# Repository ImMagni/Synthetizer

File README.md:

# Synthesizer 
A Synthesizer piano with three octaves that uses an Orpheus Pico, PCM5100 DAC, LM4810, and PAM8403 amplifiers.
 <br>

This project is a digital synthesizer keyboard capable of generating audio internally or outputting MIDI over USB. It features a screen-based user interface controlled through a rotary encoder and directional buttons.
## Features
- Volume control from the screen using a rotary encoder
- Selectable output modes: MIDI, Speakers, or Line output
- Three-octave keyboard
- Multiple waveform generation modes for audio
- Settings saves on memory
- On-screen menu system with directional navigation
- LCD feedback for current settings
## BOM
- 1× Orpheus_Pico (Raspberry Pi Pico)
- 5× Capacitor 1 µF
- 4× Capacitor 4.7 µF
- 1× Capacitor 0.1 µF
- 1× Capacitor 0.1 µF
- 2× Capacitor 10 µF
- 41× Diode 1N4148
- 1× screen ST7735R LCD
- 1× Jack audio 3.5 mm
- 2× Resistencia 10 kΩ
- 40× Cherry Switchs
- 1× Rotary Encoder with switch
- 1× PCM5100 DAC
- 1× LM4810
- 1x PAM8403
- 5x M3 Heatsets
- 5x M3x16 screws

Case|Schematic|Pcb
:-:|:-:|:-:|
|| 

-|-
:-:|:-:|
|

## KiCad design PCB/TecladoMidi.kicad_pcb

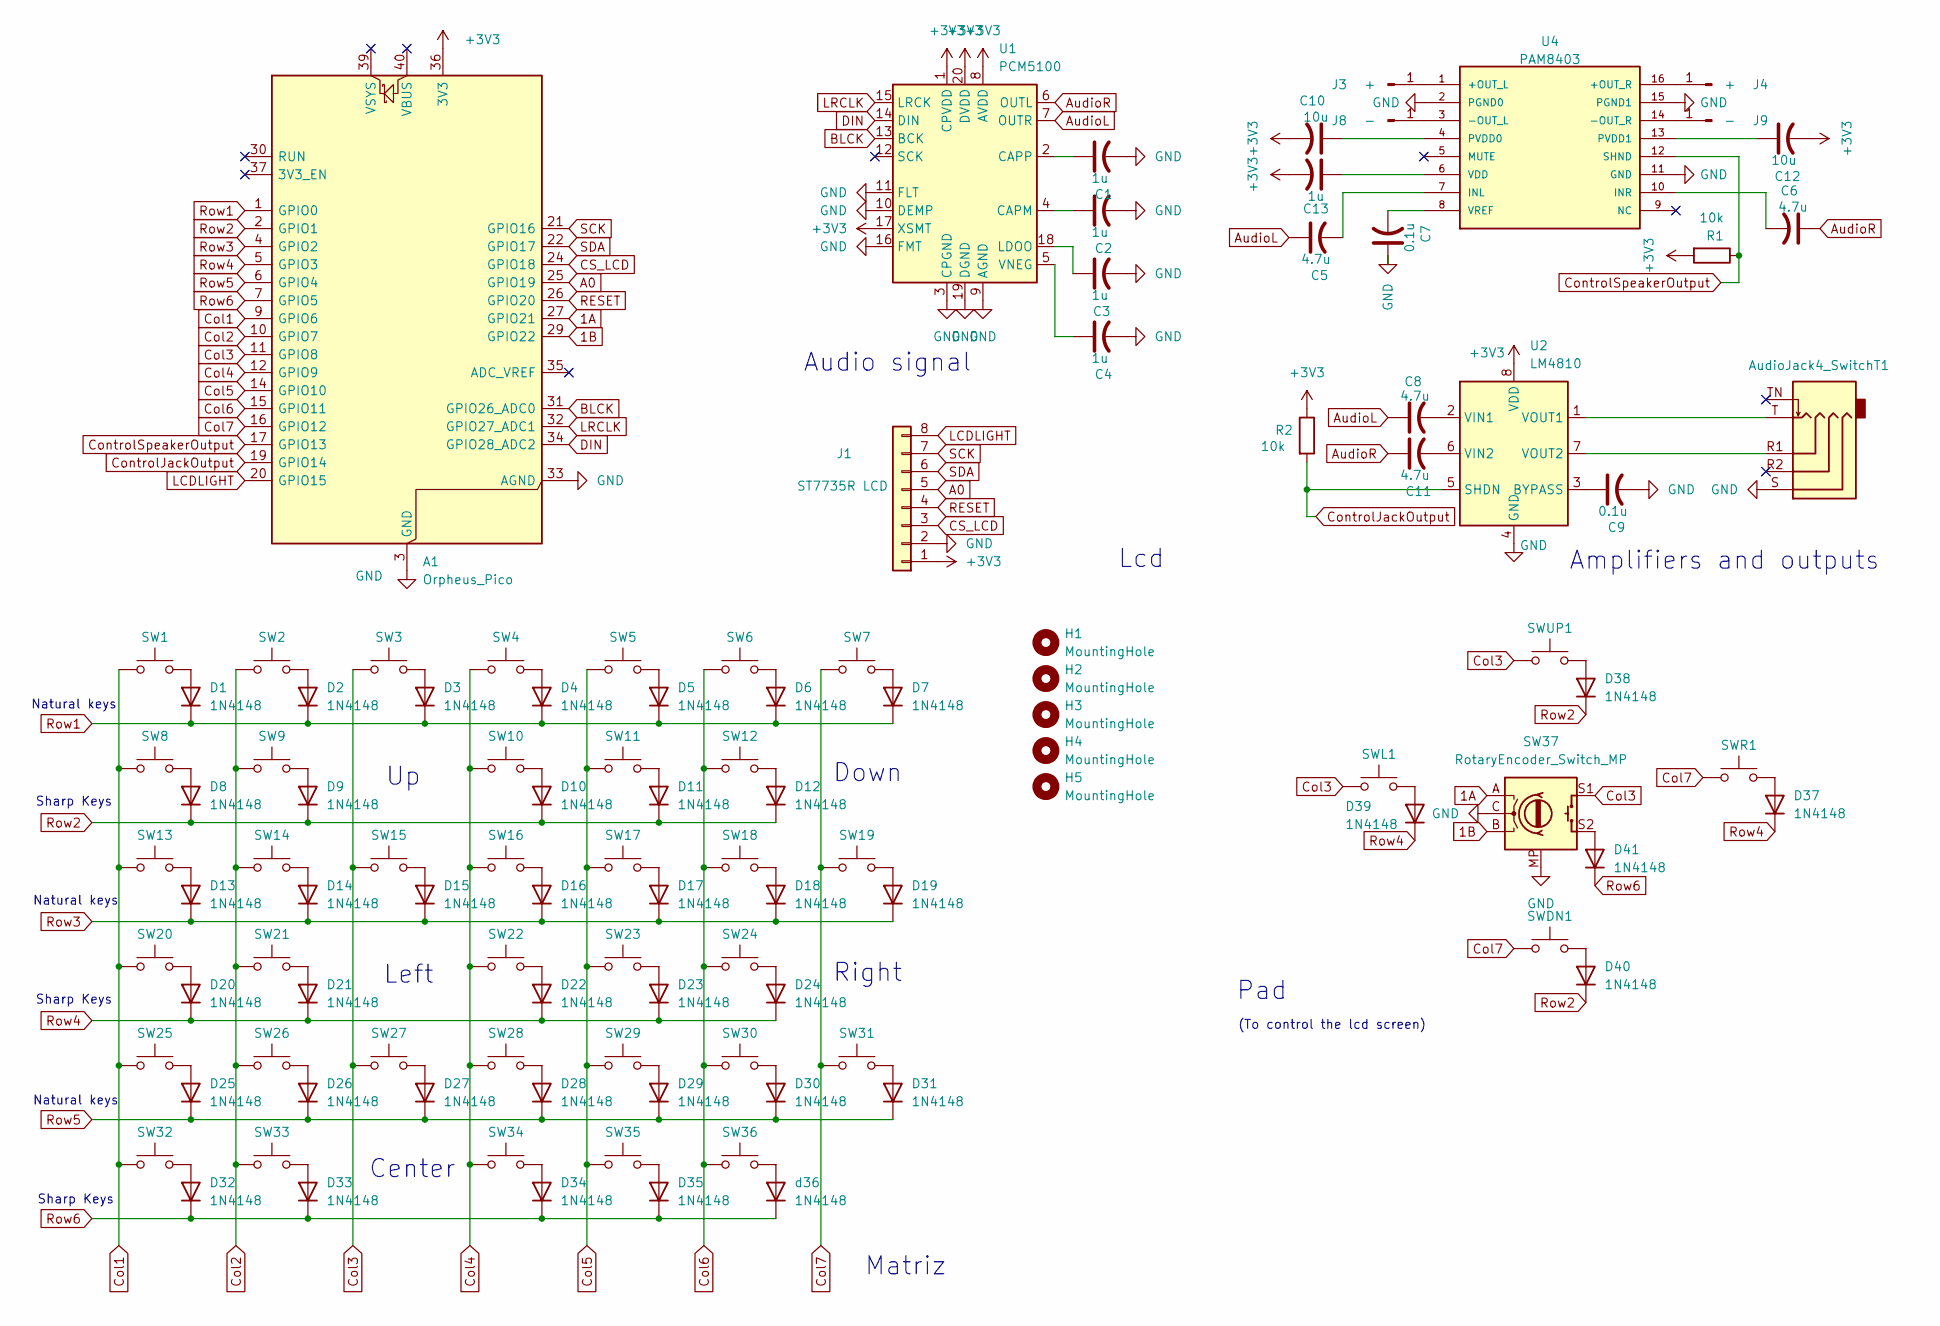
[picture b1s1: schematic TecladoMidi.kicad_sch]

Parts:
A1: Orpheus_Pico; RaspberryPi_Pico_Common_Unspecified
C1, C2, C3, C4, C13: 1u; C_Radial_D5.0mm_H5.0mm_P2.00mm
C5, C6, C8, C11: 4.7u; C_Radial_D5.0mm_H5.0mm_P2.00mm
C7: 0.1u; C_Radial_D5.0mm_H5.0mm_P2.00mm
C9: 0.1u; C_Disc_D5.0mm_W2.5mm_P2.50mm
C10, C12: 10u; C_Radial_D5.0mm_H5.0mm_P2.00mm
D1, D2, D3, D4, D5, D6, D7, D8, D9, D10, D11, D12, D13, D14, D15, D16, D17, D18, D19, D20, D21, D22, D23, D24, D25, D26, D27, D28, D29, D30, D31, D32, D33, D34, D35, D37, D38, D39, D40, D41: 1N4148; D_DO-35_SOD27_P7.62mm_Horizontal
H1, H2, H3, H4, H5: MountingHole; MountingHole_3.2mm_M3
J1: ST7735R LCD; PinHeader_1x08_P2.54mm_Vertical
J2: AudioJack4_SwitchT1; Jack_3.5mm_PJ31060-I_Horizontal
J3, J4: +; SolderWirePad_1x01_SMD_5x10mm
J8, J9: -; SolderWirePad_1x01_SMD_5x10mm
R1, R2: 10k; R_Axial_DIN0207_L6.3mm_D2.5mm_P10.16mm_Horizontal
SW1, SW2, SW3, SW4, SW5, SW6, SW7, SW8, SW9, SW10, SW11, SW12, SW13, SW14, SW15, SW16, SW17, SW18, SW19, SW20, SW21, SW22, SW23, SW24, SW25, SW26, SW27, SW28, SW29, SW30, SW31, SW32, SW33, SW34, SW35, SW36: SW_Push; SW_Cherry_MX_1.00u_PCB
SW37: RotaryEncoder_Switch_MP; RotaryEncoder_Alps_EC11E-Switch_Vertical_H20mm_MountingHoles
SWDN1: SW_Push; SW_Cherry_MX_1.00u_PCB
SWL1: SW_Push; SW_Cherry_MX_1.00u_PCB
SWR1: SW_Push; SW_Cherry_MX_1.00u_PCB
SWUP1: SW_Push; SW_Cherry_MX_1.00u_PCB
U1: PCM5100; TSSOP-20_4.4x6.5mm_P0.65mm
U2: LM4810; TSSOP-8_3x3mm_P0.65mm
U4: PAM8403; SOP-16
d36: 1N4148; D_DO-35_SOD27_P7.62mm_Horizontal

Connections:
1A: A1.27 (GPIO21), SW37.A
1B: A1.29 (GPIO22), SW37.B
+3V3: A1.36 (3V3), C10.2, C12.2, C13.2, J1.1, R1.2, R2.1, U1.1 (CPVDD), U1.8 (AVDD), U1.17 (XSMT), U1.20 (DVDD), U2.8 (VDD)
A0: A1.25 (GPIO19), J1.5
AudioL: C5.1, C8.1, U1.7 (OUTR)
AudioR: C6.1, C11.1, U1.6 (OUTL)
BLCK: A1.31 (GPIO26_ADC0), U1.13 (BCK)
CS_LCD: A1.24 (GPIO18), J1.3
Col1: A1.9 (GPIO6), SW1.1, SW8.1, SW13.1, SW20.1, SW25.1, SW32.1
Col2: A1.10 (GPIO7), SW2.1, SW9.1, SW14.1, SW21.1, SW26.1, SW33.1
Col3: A1.11 (GPIO8), SW3.1, SW15.1, SW27.1, SW37.S1, SWL1.1, SWUP1.1
Col4: A1.12 (GPIO9), SW4.1, SW10.1, SW16.1, SW22.1, SW28.1, SW34.1
Col5: A1.14 (GPIO10), SW5.1, SW11.1, SW17.1, SW23.1, SW29.1, SW35.1
Col6: A1.15 (GPIO11), SW6.1, SW12.1, SW18.1, SW24.1, SW30.1, SW36.1
Col7: A1.16 (GPIO12), SW7.1, SW19.1, SW31.1, SWDN1.1, SWR1.1
ControlJackOutput: A1.19 (GPIO14), R2.2, U2.5 (SHDN)
ControlSpeakerOutput: A1.17 (GPIO13), R1.1, U4.12 (SHND)
DIN: A1.34 (GPIO28_ADC2), U1.14 (DIN)
GND: A1.3 (GND), A1.8 (GND), A1.13 (GND), A1.18 (GND), A1.23 (GND), A1.28 (GND), A1.33 (AGND), A1.38 (GND), C1.2, C2.2, C3.2, C4.2, C7.1, C9.2, J1.2, J2.S, SW37.C, SW37.MP, U1.3 (CPGND), U1.9 (AGND), U1.10 (DEMP), U1.11 (FLT), U1.16 (FMT), U1.19 (DGND), U2.4 (GND), U4.2 (PGND0), U4.11 (GND), U4.15 (PGND1)
LCDLIGHT: A1.20 (GPIO15), J1.8
LRCLK: A1.32 (GPIO27_ADC1), U1.15 (LRCK)
unnamed: D1.2 (A), SW1.2
unnamed: D2.2 (A), SW2.2
unnamed: D3.2 (A), SW3.2
unnamed: D4.2 (A), SW4.2
unnamed: D5.2 (A), SW5.2
unnamed: D6.2 (A), SW6.2
unnamed: D7.2 (A), SW7.2
unnamed: D8.2 (A), SW8.2
unnamed: D9.2 (A), SW9.2
unnamed: D10.2 (A), SW10.2
unnamed: D11.2 (A), SW11.2
unnamed: D12.2 (A), SW12.2
unnamed: D13.2 (A), SW13.2
unnamed: D14.2 (A), SW14.2
unnamed: D15.2 (A), SW15.2
unnamed: D16.2 (A), SW16.2
unnamed: D17.2 (A), SW17.2
unnamed: D18.2 (A), SW18.2
unnamed: D19.2 (A), SW19.2
unnamed: D20.2 (A), SW20.2
unnamed: D21.2 (A), SW21.2
unnamed: D22.2 (A), SW22.2
unnamed: D23.2 (A), SW23.2
unnamed: D24.2 (A), SW24.2
unnamed: D25.2 (A), SW25.2
unnamed: D26.2 (A), SW26.2
unnamed: D27.2 (A), SW27.2
unnamed: D28.2 (A), SW28.2
unnamed: D29.2 (A), SW29.2
unnamed: D30.2 (A), SW30.2
unnamed: D31.2 (A), SW31.2
unnamed: D32.2 (A), SW32.2
unnamed: D33.2 (A), SW33.2
unnamed: D34.2 (A), SW34.2
unnamed: D35.2 (A), SW35.2
unnamed: D37.2 (A), SWR1.2
unnamed: D38.2 (A), SWUP1.2
unnamed: D39.2 (A), SWL1.2
unnamed: D40.2 (A), SWDN1.2
unnamed: D41.2 (A), SW37.S2
unnamed: J3.1, U4.1 (+OUT_L)
unnamed: J4.1, U4.16 (+OUT_R)
unnamed: J8.1, U4.3 (-OUT_L)
unnamed: J9.1, U4.14 (-OUT_R)
unnamed: C2.1, U1.4 (CAPM)
unnamed: C1.1, U1.2 (CAPP)
unnamed: C3.1, U1.18 (LDOO)
unnamed: C4.1, U1.5 (VNEG)
unnamed: C9.1, U2.3 (BYPASS)
unnamed: C8.2, U2.2 (VIN1)
unnamed: C11.2, U2.6 (VIN2)
unnamed: J2.T, U2.1 (VOUT1)
unnamed: J2.R1, U2.7 (VOUT2)
unnamed: C5.2, U4.7 (INL)
unnamed: C6.2, U4.10 (INR)
unnamed: C10.1, U4.4 (PVDD0)
unnamed: C12.1, U4.13 (PVDD1)
unnamed: C13.1, U4.6 (VDD)
unnamed: C7.2, U4.8 (VREF)
unnamed: SW36.2, d36.2 (A)
RESET: A1.26 (GPIO20), J1.4
Row1: A1.1 (GPIO0), D1.1 (K), D2.1 (K), D3.1 (K), D4.1 (K), D5.1 (K), D6.1 (K), D7.1 (K)
Row2: A1.2 (GPIO1), D8.1 (K), D9.1 (K), D10.1 (K), D11.1 (K), D12.1 (K), D38.1 (K), D40.1 (K)
Row3: A1.4 (GPIO2), D13.1 (K), D14.1 (K), D15.1 (K), D16.1 (K), D17.1 (K), D18.1 (K), D19.1 (K)
Row4: A1.5 (GPIO3), D20.1 (K), D21.1 (K), D22.1 (K), D23.1 (K), D24.1 (K), D37.1 (K), D39.1 (K)
Row5: A1.6 (GPIO4), D25.1 (K), D26.1 (K), D27.1 (K), D28.1 (K), D29.1 (K), D30.1 (K), D31.1 (K)
Row6: A1.7 (GPIO5), D32.1 (K), D33.1 (K), D34.1 (K), D35.1 (K), D41.1 (K), d36.1 (K)
SCK: A1.21 (GPIO16), J1.7
SDA: A1.22 (GPIO17), J1.6

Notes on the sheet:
Matriz
Right
Sharp Keys
(To control the lcd screen)
Amplifiers and outputs
Down
Audio signal
Lcd
Natural keys
Pad
Center
Left

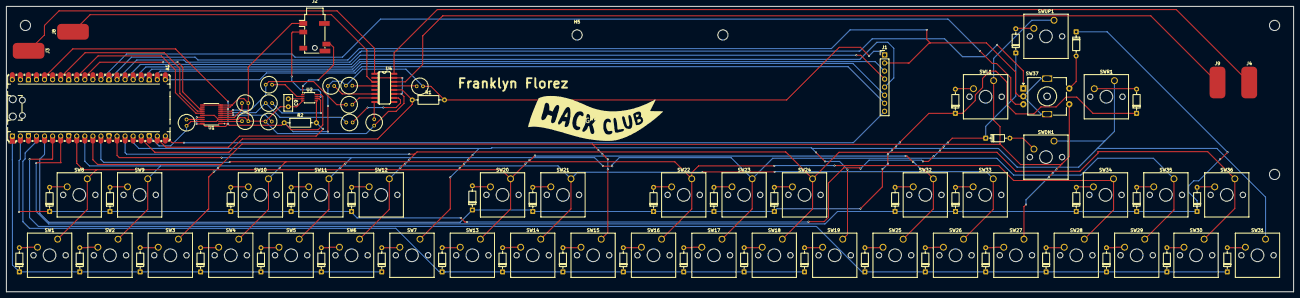
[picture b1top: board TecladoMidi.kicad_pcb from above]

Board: 2 copper layers, 406.0 x 90.0 mm, 112 parts (0 on the bottom side), 90 nets.

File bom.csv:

Reference;Value;Footprint;Product Amount;Do i have it?; Product Cost ;;link
A1;Orpheus_Pico;Module:RaspberryPi_Pico_Common_Unspecified;1;No;;;
C1,C2,C3,C4,C13;1u;Capacitor_THT:C_Radial_D5.0mm_H5.0mm_P2.00mm;5;No;;;
C5,C6,C8,C11;4.7u;Capacitor_THT:C_Radial_D5.0mm_H5.0mm_P2.00mm;4;No;;;
C7;0.1u;Capacitor_THT:C_Radial_D5.0mm_H5.0mm_P2.00mm;1;No;;;
C9;0.1u;Capacitor_THT:C_Disc_D5.0mm_W2.5mm_P2.50mm;1;No;;;
C10,C12;10u;Capacitor_THT:C_Radial_D5.0mm_H5.0mm_P2.00mm;2;No;;;
D1,D2,D3,D4,D5,D6,D7,D8,D9,D10,D11,D12,D13,D14,D15,D16,D17,D18,D19,D20,D21,D22,D23,D24,D25,D26,D27,D28,D29,D30,D31,D32,D33,D34,D35,d36,D37,D38,D39,D40,D41;1N4148;Diode_THT:D_DO-35_SOD27_P7.62mm_Horizontal;41;No;;;
J1;ST7735R LCD;Connector_PinHeader_2.54mm:PinHeader_1x08_P2.54mm_Vertical;1;No;;;
R1,R2;10k;Resistor_THT:R_Axial_DIN0207_L6.3mm_D2.5mm_P10.16mm_Horizontal;2;No;;;
SW1,SW2,SW3,SW4,SW5,SW6,SW7,SW8,SW9,SW10,SW11,SW12,SW13,SW14,SW15,SW16,SW17,SW18,SW19,SW20,SW21,SW22,SW23,SW24,SW25,SW26,SW27,SW28,SW29,SW30,SW31,SW32,SW33,SW34,SW35,SW36,SWDN1,SWL1,SWR1,SWUP1;SW_Push;Button_Switch_Keyboard:SW_Cherry_MX_1.00u_PCB;40;No;;;
;Keycaps;keyboard white keycaps;40;No;;;
SW37;RotaryEncoder_Switch_MP;Rotary_Encoder:RotaryEncoder_Alps_EC11E-Switch_Vertical_H20mm_MountingHoles;1;No;;;
U1;PCM5100;Package_SO:TSSOP-20_4.4x6.5mm_P0.65mm;1;No;;;
;;;;;;;
U2;LM4810;Package_SO:TSSOP-8_3x3mm_P0.65mm;1;No; $0,40 ;;https://es.aliexpress.com/item/1005009657867113.html?spm=a2g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
U4;PAM8403;PAM8403:SOP-16;1;No; $1,44 ; Comes in pack of 10, need 1 ;https://es.aliexpress.com/item/1005004049958533.html?spm=a2g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
J2;AudioJack4_SwitchT1;Connector_Audio:Jack_3.5mm_PJ31060-I_Horizontal;1;No; $1,73 ; Comes in pack of 10, need 1 ;https://es.aliexpress.com/item/1005008729176265.html?spm=a2g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
;PCB;PCB;1;No; $17,90 ;;jlcpcb
;;pcb shipping;;No; $24,04 ;;
;;aliexpress shipping;;No; $7,00 ;;
;;;;;;;
;;;;;;;
;;;;Total; $52,51 ; It doesnt include the 3d case ship ;
;;;;;;;
;;;;;;;
;;;;;;;

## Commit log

2025-12-12 Rename schematics.png to schematic.png
2025-12-15 Rename PCB/Gerbers.zip to Gerbers.zip
2025-12-15 Create LICENSE
2025-12-15 Update README with image and feature details
    Added image and additional features to README.
2025-12-15 Update README with corrected synthesizer description
2025-12-15 Fix spelling of 'Synthesizer' in README
2025-12-30 Enhance README with project details and features
    Expanded project description and improved feature list.
2025-12-30 Update project description in README.md
    Removed mention of real-time configuration without a computer.
2025-12-31 Rename synthesizer-piano-journal.md to journals.md
